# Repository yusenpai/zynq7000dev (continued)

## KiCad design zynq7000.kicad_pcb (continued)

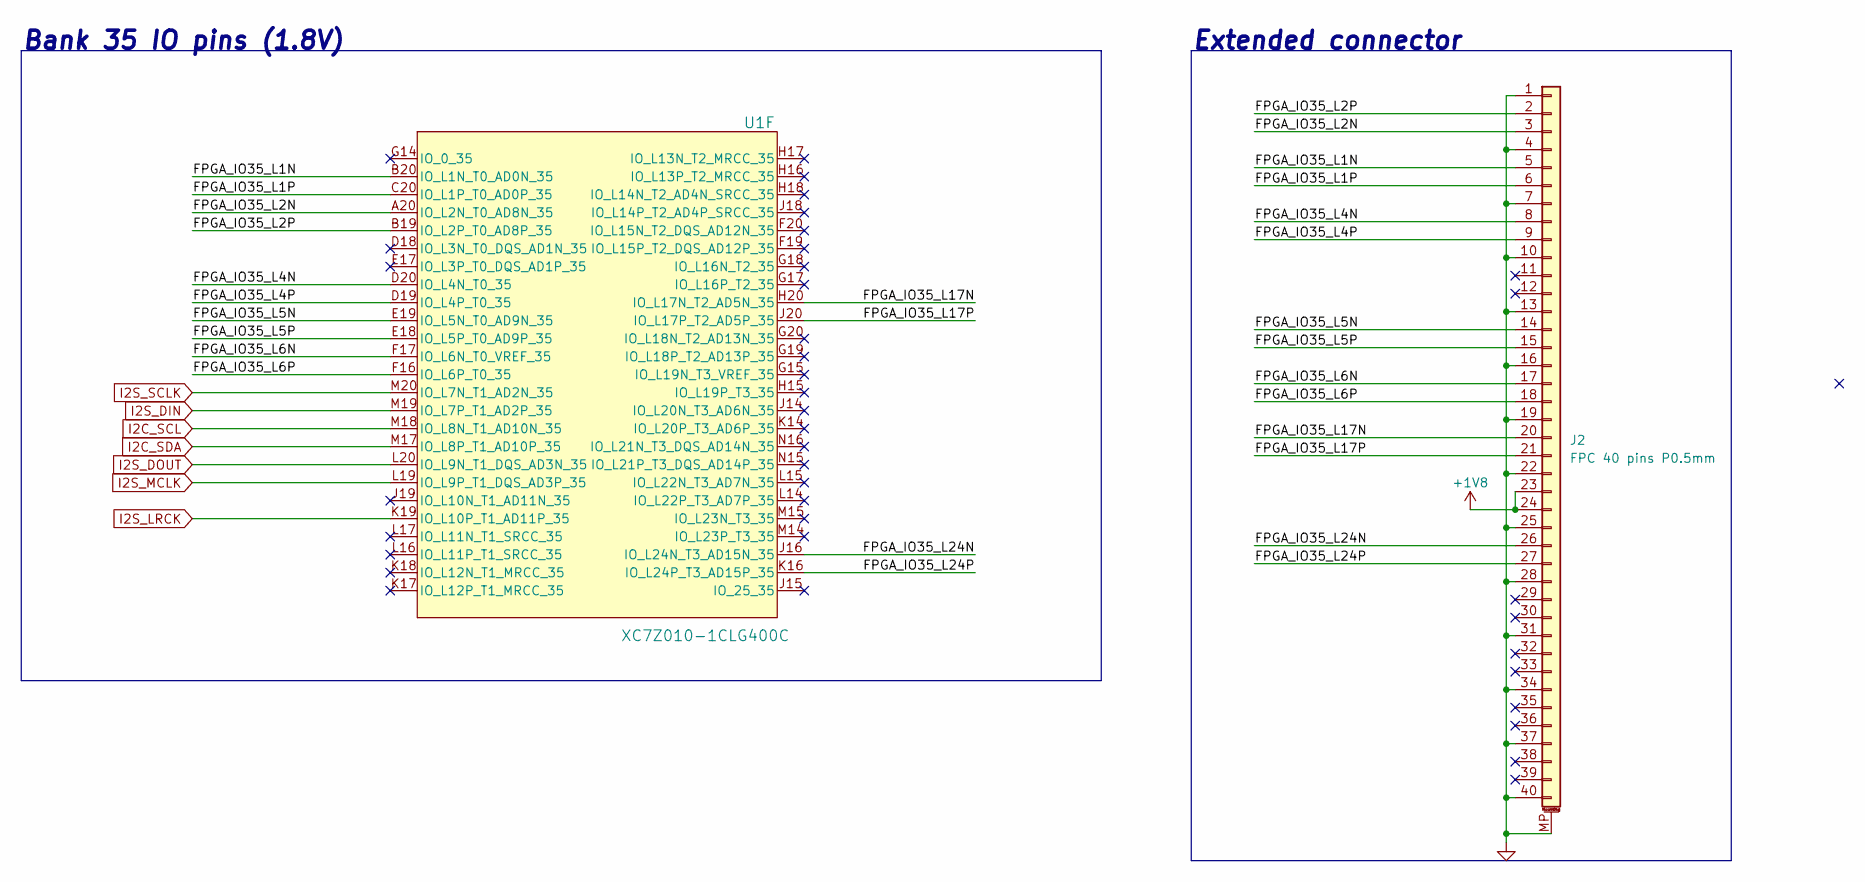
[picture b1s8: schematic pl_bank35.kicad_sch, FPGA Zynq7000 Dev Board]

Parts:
J2: FPC 40 pins P0.5mm; Amphenol_F32Q-1A7x1-11040_1x40-1MP_P0.5mm_Horizontal
U1: XC7Z010-1CLG400C; CLG400_XIL-L

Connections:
+1V8: J2.23, J2.24; also elsewhere on the board
/Bank 35 (1.8V)/FPGA_IO35_L1N: J2.5, U1.B20 (IO_L1N_T0_AD0N_35)
/Bank 35 (1.8V)/FPGA_IO35_L1P: J2.6, U1.C20 (IO_L1P_T0_AD0P_35)
/Bank 35 (1.8V)/FPGA_IO35_L2N: J2.3, U1.A20 (IO_L2N_T0_AD8N_35)
/Bank 35 (1.8V)/FPGA_IO35_L2P: J2.2, U1.B19 (IO_L2P_T0_AD8P_35)
/Bank 35 (1.8V)/FPGA_IO35_L4N: J2.8, U1.D20 (IO_L4N_T0_35)
/Bank 35 (1.8V)/FPGA_IO35_L4P: J2.9, U1.D19 (IO_L4P_T0_35)
/Bank 35 (1.8V)/FPGA_IO35_L5N: J2.14, U1.E19 (IO_L5N_T0_AD9N_35)
/Bank 35 (1.8V)/FPGA_IO35_L5P: J2.15, U1.E18 (IO_L5P_T0_AD9P_35)
/Bank 35 (1.8V)/FPGA_IO35_L6N: J2.17, U1.F17 (IO_L6N_T0_VREF_35)
/Bank 35 (1.8V)/FPGA_IO35_L6P: J2.18, U1.F16 (IO_L6P_T0_35)
/Bank 35 (1.8V)/FPGA_IO35_L17N: J2.20, U1.H20 (IO_L17N_T2_AD5N_35)
/Bank 35 (1.8V)/FPGA_IO35_L17P: J2.21, U1.J20 (IO_L17P_T2_AD5P_35)
/Bank 35 (1.8V)/FPGA_IO35_L24N: J2.26, U1.J16 (IO_L24N_T3_AD15N_35)
/Bank 35 (1.8V)/FPGA_IO35_L24P: J2.27, U1.K16 (IO_L24P_T3_AD15P_35)
GND: J2.1, J2.4, J2.7, J2.10, J2.13, J2.16, J2.19, J2.22, J2.25, J2.28, J2.31, J2.34, J2.37, J2.40, J2.MP (MountPin); also elsewhere on the board
I2C_SCL: U1.M18 (IO_L8N_T1_AD10N_35); also elsewhere on the board
I2C_SDA: U1.M17 (IO_L8P_T1_AD10P_35); also elsewhere on the board
I2S_DIN: U1.M19 (IO_L7P_T1_AD2P_35); also elsewhere on the board
I2S_DOUT: U1.L20 (IO_L9N_T1_DQS_AD3N_35); also elsewhere on the board
I2S_LRCK: U1.K19 (IO_L10P_T1_AD11P_35); also elsewhere on the board
I2S_MCLK: U1.L19 (IO_L9P_T1_DQS_AD3P_35); also elsewhere on the board
I2S_SCLK: U1.M20 (IO_L7N_T1_AD2N_35); also elsewhere on the board

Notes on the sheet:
Extended connector
Bank 35 IO pins (1.8V)

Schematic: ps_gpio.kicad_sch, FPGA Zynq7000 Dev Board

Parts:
C47: 100n; C_0402_1005Metric
D4: RED; LED_0603_1608Metric
R44, R45, R46, R47, R48, R49: 22R; R_0402_1005Metric
R50, R51: 4k7; R_0402_1005Metric
R52: 1k; R_0402_1005Metric
U1: XC7Z010-1CLG400C; CLG400_XIL-L

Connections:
+1V8: R50.1; also elsewhere on the board
/PS IO pins/ETH_TXCTL_R: R49.1, U1.F14 (PS_MIO21_501)
/PS IO pins/ETH_TXC_R: R44.1, U1.A19 (PS_MIO16_501)
/PS IO pins/ETH_TXD0_R: R45.1, U1.E14 (PS_MIO17_501)
/PS IO pins/ETH_TXD1_R: R46.1, U1.B18 (PS_MIO18_501)
/PS IO pins/ETH_TXD2_R: R47.1, U1.D10 (PS_MIO19_501)
/PS IO pins/ETH_TXD3_R: R48.1, U1.A17 (PS_MIO20_501)
ETH_MDCK: U1.C10 (PS_MIO52_501); also elsewhere on the board
ETH_MDIO: U1.C11 (PS_MIO53_501); also elsewhere on the board
ETH_RXCK: U1.B17 (PS_MIO22_501); also elsewhere on the board
ETH_RXCT: U1.D13 (PS_MIO27_501); also elsewhere on the board
ETH_RXD0: U1.D11 (PS_MIO23_501); also elsewhere on the board
ETH_RXD1: U1.A16 (PS_MIO24_501); also elsewhere on the board
ETH_RXD2: U1.F15 (PS_MIO25_501); also elsewhere on the board
ETH_RXD3: U1.A15 (PS_MIO26_501); also elsewhere on the board
ETH_TXCK: R44.2; also elsewhere on the board
ETH_TXCT: R49.2; also elsewhere on the board
ETH_TXD0: R45.2; also elsewhere on the board
ETH_TXD1: R46.2; also elsewhere on the board
ETH_TXD2: R47.2; also elsewhere on the board
ETH_TXD3: R48.2; also elsewhere on the board
FPGA_PS_VMODE1: U1.D5 (PS_MIO8_500); also elsewhere on the board
GND: C47.2, D4.1 (K), R51.2; also elsewhere on the board
unnamed: D4.2 (A), R52.2
unnamed: C47.1, R50.2, R51.1, U1.E11 (PS_MIO_VREF_501)
PS_LED: R52.1, U1.D8 (PS_MIO7_500); also elsewhere on the board
QSPI0_CK: U1.A5 (PS_MIO6_500); also elsewhere on the board
QSPI0_CSN: U1.A7 (PS_MIO1_500); also elsewhere on the board
QSPI0_D0: U1.B8 (PS_MIO2_500); also elsewhere on the board
QSPI0_D1: U1.D6 (PS_MIO3_500); also elsewhere on the board
QSPI0_D2: U1.B7 (PS_MIO4_500); also elsewhere on the board
QSPI0_D3: U1.A6 (PS_MIO5_500); also elsewhere on the board
SDIO1_CD: U1.E6 (PS_MIO0_500); also elsewhere on the board
SDIO1_CLK: U1.D9 (PS_MIO12_500); also elsewhere on the board
SDIO1_CMD: U1.C6 (PS_MIO11_500); also elsewhere on the board
SDIO1_D0: U1.E9 (PS_MIO10_500); also elsewhere on the board
SDIO1_D1: U1.E8 (PS_MIO13_500); also elsewhere on the board
SDIO1_D2: U1.C5 (PS_MIO14_500); also elsewhere on the board
SDIO1_D3: U1.C8 (PS_MIO15_500); also elsewhere on the board
ULPI_CLK: U1.B12 (PS_MIO48_501); also elsewhere on the board
ULPI_D0: U1.F13 (PS_MIO44_501); also elsewhere on the board
ULPI_D1: U1.B15 (PS_MIO45_501); also elsewhere on the board
ULPI_D2: U1.D16 (PS_MIO46_501); also elsewhere on the board
ULPI_D3: U1.B14 (PS_MIO47_501); also elsewhere on the board
ULPI_D4: U1.D14 (PS_MIO40_501); also elsewhere on the board
ULPI_D5: U1.C12 (PS_MIO49_501); also elsewhere on the board
ULPI_D6: U1.B13 (PS_MIO50_501); also elsewhere on the board
ULPI_D7: U1.B9 (PS_MIO51_501); also elsewhere on the board
ULPI_DIR: U1.C17 (PS_MIO41_501); also elsewhere on the board
ULPI_NXT: U1.A9 (PS_MIO43_501); also elsewhere on the board
ULPI_STP: U1.E12 (PS_MIO42_501); also elsewhere on the board

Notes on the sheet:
PS IO pins

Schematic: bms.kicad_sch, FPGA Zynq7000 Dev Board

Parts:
C85, C88, C90, C91: 4u7; C_0402_1005Metric
C86: 47n; C_0402_1005Metric
C87: 10u; C_0603_1608Metric
C89: 10u; C_0402_1005Metric
D5: BLUE; LED_0603_1608Metric
D6: GREEN; LED_0603_1608Metric
J6: USB_C_Receptacle_USB2.0_16P; USB_C_Receptacle_GCT_USB4105-xx-A_16P_TopMnt_Horizontal
J7: MX_1.25mm; Molex_PicoBlade_53398-0671_1x06-1MP_P1.25mm_Vertical
L6: 1u; L_Chilisin_BMRA00040420
R61, R62, R66: 5k1; R_0402_1005Metric
R63: 0R; R_0402_1005Metric; not fitted
R64, R65: 2k2; R_0402_1005Metric
R67: 30k; R_0402_1005Metric
U5: BQ25601; WQFN-24-1EP_4x4mm_P0.5mm_BQ25601

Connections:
+BATT: C89.1, J7.1, J7.2, U5.13 (BAT), U5.14 (BAT)
/BMS/BATT_THER: J7.5, R66.2, R67.1, U5.11 (TS)
GND: C85.2, C87.2, C88.2, C89.2, C90.2, C91.2, J6.A1 (GND), J6.A12 (GND), J6.B1 (GND), J6.B12 (GND), J6.S1 (SHIELD), J7.3, J7.4, R61.1, R62.1, R67.2, U5.2 (PSEL), U5.9 (~CE), U5.17 (GND), U5.18 (GND), U5.25 (GND); also elsewhere on the board
unnamed: C86.1, L6.1, U5.19 (SW), U5.20 (SW)
unnamed: D5.1 (K), R64.2
unnamed: D6.1 (K), R65.1
unnamed: J6.A5 (CC1), R61.2
unnamed: J6.B5 (CC2), R62.2
unnamed: J6.A6 (D+), J6.B6 (D+), R63.2
unnamed: J6.A7 (D-), J6.B7 (D-), R63.1
unnamed: C86.2, U5.21 (BTST)
unnamed: C90.1, C91.1, U5.23 (PMID)
unnamed: C88.1, R66.1, U5.22 (REGN)
unnamed: R64.1, U5.4 (STAT)
unnamed: R65.2, U5.3 (~PG)
PMIC_I2C_SCL: U5.5 (SCL); also elsewhere on the board
PMIC_I2C_SDA: U5.6 (SDA); also elsewhere on the board
PMIC_PWRON: U5.12 (~QON); also elsewhere on the board
VBUS: C85.1, J6.A4 (VBUS), J6.A9 (VBUS), J6.B4 (VBUS), J6.B9 (VBUS), U5.1 (VAC), U5.24 (VBUS)
VSYS: C87.1, D5.2 (A), D6.2 (A), L6.2, U5.15 (SYS), U5.16 (SYS); also elsewhere on the board

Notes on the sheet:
PSEL = 0 : ILIM = 2.4A CE = 0 : charge enable PMIC_PWRON = 0 for 1s: BATFET turn on. PMIC turn on. PMIC_PWRON = 0 for 4s: PMIC turn off. PMIC_PWRON = 0 for 8s: system reset.
BMS

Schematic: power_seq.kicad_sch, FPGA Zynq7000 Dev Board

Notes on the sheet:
+1.0V
From PMIC
BUCK
+3.3V
1.4A
LDO
PS: AUX, PLL, Bank 501 PL: AUX, Bank 35 USB PHY, ETH PHY, Audio CODEC
6A discharge 2A charge
4.5A
PS: Bank 502 2xDDR3 DRAM
0.5A
0.8A
+1.35V
+0.675V
DDR3L VTT rail
From BMS
Power Sequence
Power up: 1 -> 2 -> 3 -> 4 Power down: 4 -> 3 -> 2 -> 1
USB-C Connector
+5V
+1.8V
1.25A
0.2A
Power Tree
PS: Bank 500 PL: Bank 34 QSPI Flash, SD Card
DDR3L reference
1.1A
Ramp-up time must be smaller than 50ms
BMS
Battery
+3.5V -> +4.2V
0.6A
+3.5V
PS: Internal PL: Internal, BRAM
3.5V
3.8A
Audio CODEC

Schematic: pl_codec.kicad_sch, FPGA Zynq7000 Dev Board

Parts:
C48, C49, C50, C51, C54: 100n; C_0402_1005Metric
C52, C53, C55: 1u; C_0402_1005Metric
C56, C57: 22u; C_0603_1608Metric
J4: PJ320D; Jack_3.5mm_PJ320D_Horizontal
R53: 2k2; R_0402_1005Metric
R54, R55: 4k7; R_0402_1005Metric
U4: SGTL5000XNLA3; QFN-20-1EP_3x3mm_P0.4mm_EP1.65x1.65mm

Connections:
+1V8: C48.1, C49.1, R54.1, R55.1, U4.12 (VDDIO), U4.20 (VDDD); also elsewhere on the board
+1V8A: C50.1, U4.3 (VDDA); also elsewhere on the board
/Audio CODEC/LINEIN_L: C53.1, C57.2, J4.T
/Audio CODEC/LINEIN_R: C52.1, C56.2, J4.R1
/Audio CODEC/MIC_IN: C54.1, J4.S, R53.1
GND: C48.2, C49.2, C50.2, C51.1, C55.2, U4.21 (GND); also elsewhere on the board
I2C_SCL: R55.2, U4.19 (CTRL_CLK); also elsewhere on the board
I2C_SDA: R54.2, U4.18 (CTRL_DATA); also elsewhere on the board
I2S_DIN: U4.17 (I2S_DIN); also elsewhere on the board
I2S_DOUT: U4.16 (I2S_DOUT); also elsewhere on the board
I2S_LRCK: U4.14 (I2S_LRCLK); also elsewhere on the board
I2S_MCLK: U4.13 (SYS_MCLK); also elsewhere on the board
I2S_SCLK: U4.15 (I2S_SCLK); also elsewhere on the board
unnamed: C57.1, U4.4 (HP_L)
unnamed: C56.1, U4.1 (HP_R)
unnamed: J4.R2, U4.2 (HP_VGND)
unnamed: C53.2, U4.9 (LINEIN_L)
unnamed: C52.2, U4.8 (LINEIN_R)
unnamed: C54.2, U4.10 (MIC)
unnamed: C55.1, R53.2, U4.11 (MIC_BIAS)
unnamed: C51.2, U4.5 (VAG)

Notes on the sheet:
Audio CODEC

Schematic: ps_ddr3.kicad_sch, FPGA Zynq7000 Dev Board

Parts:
C1, C2, C3, C4, C5, C6, C7, C8, C10, C11, C12, C13, C14, C15, C16, C17, C18, C19, C20, C21, C22, C23, C24, C25, C26: 1u; C_0402_1005Metric
C9: 470n; C_0402_1005Metric; not fitted
C29, C30: 10u; C_0402_1005Metric
C31, C32: 4u7; C_0402_1005Metric
C33, C34, C35, C36, C37, C38, C39, C40, C41, C42, C43, C44: 100n; C_0402_1005Metric
R3, R4: 240R; R_0402_1005Metric
R6, R7, R8: 4k7; R_0402_1005Metric
R9, R10, R11, R12, R13, R14, R15, R16, R17, R18, R20, R21, R22, R23, R24, R25, R26, R27, R28, R29, R30, R31, R32, R33: 60R4; R_0402_1005Metric
R19: 120R; R_0402_1005Metric
U2, U3: H5TC2G83EFR-xxA; FBGA-78_7.5x11mm_Layout2x3x13_P0.8mm

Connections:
+0V675: C29.1, C30.1, C31.1, C32.1, C33.1, C34.1, C35.1, C36.1, C37.1, C38.1, C39.1, C40.1, C41.1, C42.1, C43.1, C44.1, R9.1, R10.1, R11.1, R12.1, R13.1, R14.1, R15.1, R16.1, R17.1, R18.1, R20.1, R21.1, R22.1, R23.1, R24.1, R25.1, R26.1, R27.1, R28.1, R29.1, R30.1, R31.1, R32.1, R33.1; also elsewhere on the board
+1V35: C1.1, C2.1, C3.1, C4.1, C5.1, C6.1, C7.1, C8.1, C9.1, C10.1, C11.1, C12.1, C13.1, C14.1, C15.1, C16.1, C17.1, C18.1, C19.1, C20.1, C21.1, C22.1, C23.1, C24.1, U2.A2 (VDD), U2.A9 (VDD), U2.B9 (VDDQ), U2.C1 (VDDQ), U2.D7 (VDD), U2.E2 (VDDQ), U2.E9 (VDDQ), U2.G2 (VDD), U2.G8 (VDD), U2.K1 (VDD), U2.K9 (VDD), U2.M1 (VDD), U2.M9 (VDD), U3.A2 (VDD), U3.A9 (VDD), U3.B9 (VDDQ), U3.C1 (VDDQ), U3.D7 (VDD), U3.E2 (VDDQ), U3.E9 (VDDQ), U3.G2 (VDD), U3.G8 (VDD), U3.K1 (VDD), U3.K9 (VDD), U3.M1 (VDD), U3.M9 (VDD); also elsewhere on the board
DRAM_A0: R16.2, U2.K3 (A0), U3.K3 (A0); also elsewhere on the board
DRAM_A1: R18.2, U2.L7 (A1), U3.L7 (A1); also elsewhere on the board
DRAM_A2: R21.2, U2.L3 (A2), U3.L3 (A2); also elsewhere on the board
DRAM_A3: R23.2, U2.K2 (A3), U3.K2 (A3); also elsewhere on the board
DRAM_A4: R25.2, U2.L8 (A4), U3.L8 (A4); also elsewhere on the board
DRAM_A5: R27.2, U2.L2 (A5), U3.L2 (A5); also elsewhere on the board
DRAM_A6: R29.2, U2.M8 (A6), U3.M8 (A6); also elsewhere on the board
DRAM_A7: R31.2, U2.M2 (A7), U3.M2 (A7); also elsewhere on the board
DRAM_A8: R33.2, U2.N8 (A8), U3.N8 (A8); also elsewhere on the board
DRAM_A9: R9.2, U2.M3 (A9), U3.M3 (A9); also elsewhere on the board
DRAM_A10: R11.2, U2.H7 (A10/AP), U3.H7 (A10/AP); also elsewhere on the board
DRAM_A11: R13.2, U2.M7 (A11), U3.M7 (A11); also elsewhere on the board
DRAM_A12: R15.2, U2.K7 (A12/BC#), U3.K7 (A12/BC#); also elsewhere on the board
DRAM_A13: R17.2, U2.N3 (A13), U3.N3 (A13); also elsewhere on the board
DRAM_A14: R20.2, U2.N7 (A14), U3.N7 (A14); also elsewhere on the board
DRAM_BA0: R10.2, U2.J2 (BA0), U3.J2 (BA0); also elsewhere on the board
DRAM_BA1: R12.2, U2.K8 (BA1), U3.K8 (BA1); also elsewhere on the board
DRAM_BA2: R14.2, U2.J3 (BA2), U3.J3 (BA2); also elsewhere on the board
DRAM_CASN: R28.2, U2.G3 (CAS#), U3.G3 (CAS#); also elsewhere on the board
DRAM_CKE: R6.1, R22.2, U2.G9 (CKE), U3.G9 (CKE); also elsewhere on the board
DRAM_CLK_N: R19.2, U2.G7 (CK#), U3.G7 (CK#); also elsewhere on the board
DRAM_CLK_P: R19.1, U2.F7 (CK), U3.F7 (CK); also elsewhere on the board
DRAM_CSN: R7.1, R32.2, U2.H2 (CS#), U3.H2 (CS#); also elsewhere on the board
DRAM_DM0: U2.B7 (DM/TDQS); also elsewhere on the board
DRAM_DM1: U3.B7 (DM/TDQS); also elsewhere on the board
DRAM_DQ0: U2.B3 (DQ0); also elsewhere on the board
DRAM_DQ1: U2.C7 (DQ1); also elsewhere on the board
DRAM_DQ2: U2.D2 (DQ6); also elsewhere on the board
DRAM_DQ3: U2.C8 (DQ3); also elsewhere on the board
DRAM_DQ4: U2.E3 (DQ4); also elsewhere on the board
DRAM_DQ5: U2.E8 (DQ5); also elsewhere on the board
DRAM_DQ6: U2.C2 (DQ2); also elsewhere on the board
DRAM_DQ7: U2.E7 (DQ7); also elsewhere on the board
DRAM_DQ8: U3.B3 (DQ0); also elsewhere on the board
DRAM_DQ9: U3.C7 (DQ1); also elsewhere on the board
DRAM_DQ10: U3.C2 (DQ2); also elsewhere on the board
DRAM_DQ11: U3.C8 (DQ3); also elsewhere on the board
DRAM_DQ12: U3.E3 (DQ4); also elsewhere on the board
DRAM_DQ13: U3.E8 (DQ5); also elsewhere on the board
DRAM_DQ14: U3.D2 (DQ6); also elsewhere on the board
DRAM_DQ15: U3.E7 (DQ7); also elsewhere on the board
DRAM_DQS0_N: U2.D3 (DQS#); also elsewhere on the board
DRAM_DQS0_P: U2.C3 (DQS); also elsewhere on the board
DRAM_DQS1_N: U3.D3 (DQS#); also elsewhere on the board
DRAM_DQS1_P: U3.C3 (DQS); also elsewhere on the board
DRAM_ODT: R30.2, U2.G1 (ODT), U3.G1 (ODT); also elsewhere on the board
DRAM_RASN: R26.2, U2.F3 (RAS#), U3.F3 (RAS#); also elsewhere on the board
DRAM_RSTN: R8.1, U2.N2 (RESET#), U3.N2 (RESET#); also elsewhere on the board
DRAM_WEN: R24.2, U2.H3 (WE#), U3.H3 (WE#); also elsewhere on the board
GND: C1.2, C2.2, C3.2, C4.2, C5.2, C6.2, C7.2, C8.2, C9.2, C10.2, C11.2, C12.2, C13.2, C14.2, C15.2, C16.2, C17.2, C18.2, C19.2, C20.2, C21.2, C22.2, C23.2, C24.2, C25.2, C26.2, C29.2, C30.2, C31.2, C32.2, C33.2, C34.2, C35.2, C36.2, C37.2, C38.2, C39.2, C40.2, C41.2, C42.2, C43.2, C44.2, R3.2, R4.2, R6.2, R7.2, R8.2, U2.A1 (VSS), U2.A8 (VSS), U2.B1 (VSS), U2.B2 (VSSQ), U2.B8 (VSSQ), U2.C9 (VSSQ), U2.D1 (VSSQ), U2.D8 (VSS), U2.D9 (VSSQ), U2.F2 (VSS), U2.F8 (VSS), U2.J1 (VSS), U2.J9 (VSS), U2.L1 (VSS), U2.L9 (VSS), U2.N1 (VSS), U2.N9 (VSS), U3.A1 (VSS), U3.A8 (VSS), U3.B1 (VSS), U3.B2 (VSSQ), U3.B8 (VSSQ), U3.C9 (VSSQ), U3.D1 (VSSQ), U3.D8 (VSS), U3.D9 (VSSQ), U3.F2 (VSS), U3.F8 (VSS), U3.J1 (VSS), U3.J9 (VSS), U3.L1 (VSS), U3.L9 (VSS), U3.N1 (VSS), U3.N9 (VSS); also elsewhere on the board
unnamed: R3.1, U2.H8 (ZQ)
unnamed: R4.1, U3.H8 (ZQ)
VREF_DDR: C25.1, C26.1, U2.E1 (VREFDQ), U2.J8 (VREFCA), U3.E1 (VREFDQ), U3.J8 (VREFCA); also elsewhere on the board

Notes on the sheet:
need termination for data mask ?
DDR3L-2
DDR3L-1
VTT bypass cap. and termination

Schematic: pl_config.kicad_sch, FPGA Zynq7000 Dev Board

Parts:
C45, C46: 100n; C_0402_1005Metric
D1: RED; LED_0603_1608Metric
D2: GREEN; LED_0603_1608Metric
D3: BLUE; LED_0603_1608Metric
J3: Header 2.54mm; PinHeader_1x06_P2.54mm_Vertical
R34, R36, R37: 10k; R_0402_1005Metric
R35, R38, R40, R43: 4k7; R_0402_1005Metric
R39, R41: 1k; R_0402_1005Metric
R42: 330R; R_0402_1005Metric
SW1, SW2: SW_Push; SW_Push_1P1T_NO_Vertical_Wuerth_434133025816
U1: XC7Z010-1CLG400C; CLG400_XIL-L

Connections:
+3V3: R34.1, R35.1, R36.1, R37.1, R38.1, R39.1, R40.2, R42.1, U1.M6 (CFGBVS_0); also elsewhere on the board
/PL Configuration/FPGA_PL_DONE: D3.2 (A), R42.2, U1.R11 (DONE_0)
/PL Configuration/FPGA_PL_INIT_B: D1.1 (K), D2.2 (A), R39.2, U1.R10 (INIT_B_0)
/PL Configuration/FPGA_PL_PROGRAM_B: C45.2, R38.2, SW1.2, U1.L6 (PROGRAM_B_0)
FPGA_PS_CLK_40MHz: U1.E7 (PS_CLK_500); also elsewhere on the board
FPGA_PS_SRST_B: C46.2, J3.1, R35.2, SW2.2, U1.B10 (PS_SRST_B_501); also elsewhere on the board
FPGA_TCK: J3.2, R36.2, U1.F9 (TCK_0); also elsewhere on the board
FPGA_TDI: J3.4, U1.G6 (TDI_0); also elsewhere on the board
FPGA_TDO: J3.3, U1.F6 (TDO_0); also elsewhere on the board
FPGA_TMS: J3.5, R37.2, U1.J6 (TMS_0); also elsewhere on the board
GND: C45.1, C46.1, J3.6, R41.2, R43.2, SW1.1, SW2.1; also elsewhere on the board
unnamed: D1.2 (A), R40.1
unnamed: D2.1 (K), R41.1
unnamed: D3.1 (K), R43.1
PMIC_MCU_NRST: R34.2, U1.C7 (PS_POR_B_500); also elsewhere on the board

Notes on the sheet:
PL Configuration
Configuration Block and JTAG conn.
OK PS_POR_B input is required to be asserted to GND during the power-on sequence OK The PS system reset (PS_SRST_B) is an active-Low signal that is mostly used for debugging proposes. OK PS_SRST_B must be High to begin the boot process OK 30MHz < PS_CLK < 60MHz OK TMS and TCK have 10k pull up OK PR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
DONE = 1: Done configuration INIT_B = 0: Open-drain, initialization of configuration memory PROGRAM_B = 0: Asynchronous reset of configuration logic CFGBVS = VCCO_0: MUST DO. Select the voltage level of 3.3V for configuration bank

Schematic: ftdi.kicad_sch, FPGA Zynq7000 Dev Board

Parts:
C157, C168: 4u7; C_0402_1005Metric
C158, C159, C160, C161, C162, C163, C164, C165, C166, C167, C169: 100n; C_0402_1005Metric
C170, C171: 10p; C_0402_1005Metric
FB1: 600R; L_0603_1608Metric
J11: USB_C_Receptacle_USB2.0_16P; USB_C_Receptacle_GCT_USB4105-xx-A_16P_TopMnt_Horizontal
R87, R88: 5k1; R_0402_1005Metric
R89, R95: 2k; R_0402_1005Metric
R90, R92, R93, R94: 10k; R_0402_1005Metric
R91: 1k; R_0402_1005Metric
U9: FT4232H; LQFP-64_10x10mm_P0.5mm
U10: AT93C46-10SU-2.7-T; SOIC8_4P9X3P9MC_MCH
Y2: 12MHz; Crystal_SMD_3225-4Pin_3.2x2.5mm

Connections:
+1V8_FTDI: C165.1, C166.1, C167.1, C168.1, U9.12 (VCORE), U9.37 (VCORE), U9.49 (VREGOUT), U9.64 (VCORE)
+3V3: C160.1, C161.1, C162.1, C163.1, C164.1, C169.1, FB1.1, R91.1, R92.1, R93.1, R94.1, U9.20 (VCCIO), U9.21 (ADBUS4), U9.31 (VCCIO), U9.42 (VCCIO), U9.50 (VREGIN), U9.56 (VCCIO), U10.2 (VCC), U10.8 (ORG); also elsewhere on the board
+3V3_PLL: C157.1, C158.1, C159.1, FB1.2, U9.4 (VPHY), U9.9 (VPLL)
/FTDI/FTDI_EEPROM_CS: R92.2, U9.63 (EECS), U10.3 (CS)
/FTDI/FTDI_EEPROM_DATA: R95.2, U9.61 (EEDATA), U10.5 (DI)
/FTDI/FTDI_EEPROM_SCK: R93.2, U9.62 (EECLK), U10.4 (SK)
/FTDI/USB_JTAG_D+: J11.A6 (D+), J11.B6 (D+), U9.8 (DP)
/FTDI/USB_JTAG_D-: J11.A7 (D-), J11.B7 (D-), U9.7 (DM)
FPGA_PS_SRST_B: U9.23 (ADBUS6); also elsewhere on the board
FPGA_TCK: U9.16 (ADBUS0); also elsewhere on the board
FPGA_TDI: U9.17 (ADBUS1); also elsewhere on the board
FPGA_TDO: U9.18 (ADBUS2); also elsewhere on the board
FPGA_TMS: U9.19 (ADBUS3); also elsewhere on the board
GND: C157.2, C158.2, C159.2, C160.2, C161.2, C162.2, C163.2, C164.2, C165.2, C166.2, C167.2, C168.2, C169.2, C170.2, C171.2, J11.A1 (GND), J11.A12 (GND), J11.B1 (GND), J11.B12 (GND), R87.2, R88.2, R89.2, U9.1 (GND), U9.5 (GND), U9.10 (AGND), U9.11 (GND), U9.13 (TEST), U9.15 (GND), U9.25 (GND), U9.35 (GND), U9.47 (GND), U9.51 (GND), U10.7 (GND), Y2.2, Y2.4; also elsewhere on the board
unnamed: J11.A5 (CC1), R87.1
unnamed: J11.B5 (CC2), R88.1
unnamed: R89.1, R90.2
unnamed: C170.1, U9.2 (OSCI), Y2.3
unnamed: C171.1, U9.3 (OSCO), Y2.1
unnamed: R90.1, U9.6 (REF)
unnamed: R91.2, U9.14 (~RESET)
unnamed: R94.2, R95.1, U10.6 (DO)
UART1_RX: U9.26 (BDBUS0); also elsewhere on the board
UART1_TX: U9.27 (BDBUS1); also elsewhere on the board
UART2_RX: U9.38 (CDBUS0); also elsewhere on the board
UART2_TX: U9.39 (CDBUS1); also elsewhere on the board
UART3_RX: U9.48 (DDBUS0); also elsewhere on the board
UART3_TX: U9.52 (DDBUS1); also elsewhere on the board

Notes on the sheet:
FTDI USB-JTAG

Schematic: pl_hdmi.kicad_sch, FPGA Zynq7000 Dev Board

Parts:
J12: HDMI_A_1.4; HDMI_A_Molex_208658-1001_Horizontal
Q1, Q2, Q3: 2N7002; SOT-23
R96, R97, R98, R99, R100: 4k7; R_0402_1005Metric

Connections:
+3V3: Q1.1 (G), Q2.1 (G), R96.1, R97.1, R100.1; also elsewhere on the board
/HDMI/HDMI_HPD: J12.19 (HPD/HEAC-), Q3.1 (G)
/HDMI/HDMI_I2C_SCL_50: J12.15 (SCL), Q1.3 (D), R99.2
/HDMI/HDMI_I2C_SDA_50: J12.16 (SDA), Q2.3 (D), R98.2
GND: J12.2 (D2S), J12.5 (D1S), J12.8 (D0S), J12.11 (CKS), J12.17 (GND), J12.SH, Q3.2 (S); also elsewhere on the board
HDMI_CEC: J12.13 (CEC); also elsewhere on the board
HDMI_CLK_N: J12.12 (CK-); also elsewhere on the board
HDMI_CLK_P: J12.10 (CK+); also elsewhere on the board
HDMI_DAT0_N: J12.9 (D0-); also elsewhere on the board
HDMI_DAT0_P: J12.7 (D0+); also elsewhere on the board
HDMI_DAT1_N: J12.6 (D1-); also elsewhere on the board
HDMI_DAT1_P: J12.4 (D1+); also elsewhere on the board
HDMI_DAT2_N: J12.3 (D2-); also elsewhere on the board
HDMI_DAT2_P: J12.1 (D2+); also elsewhere on the board
HDMI_HP_DET: Q3.3 (D), R100.2; also elsewhere on the board
HDMI_I2C_SCL: Q1.2 (S), R96.2; also elsewhere on the board
HDMI_I2C_SDA: Q2.2 (S), R97.2; also elsewhere on the board
VBUS1: J12.18 (+5V), R98.1, R99.1; also elsewhere on the board

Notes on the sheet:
HDMI

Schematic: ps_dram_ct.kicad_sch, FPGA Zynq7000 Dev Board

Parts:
C27, C28: 100n; C_0402_1005Metric
R2, R5: 120R; R_0402_1005Metric
U1: XC7Z010-1CLG400C; CLG400_XIL-L

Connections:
+1V35: R2.1; also elsewhere on the board
DRAM_A0: U1.N2 (PS_DDR_A0_502); also elsewhere on the board
DRAM_A1: U1.K2 (PS_DDR_A1_502); also elsewhere on the board
DRAM_A2: U1.M3 (PS_DDR_A2_502); also elsewhere on the board
DRAM_A3: U1.K3 (PS_DDR_A3_502); also elsewhere on the board
DRAM_A4: U1.M4 (PS_DDR_A4_502); also elsewhere on the board
DRAM_A5: U1.L1 (PS_DDR_A5_502); also elsewhere on the board
DRAM_A6: U1.L4 (PS_DDR_A6_502); also elsewhere on the board
DRAM_A7: U1.K4 (PS_DDR_A7_502); also elsewhere on the board
DRAM_A8: U1.K1 (PS_DDR_A8_502); also elsewhere on the board
DRAM_A9: U1.J4 (PS_DDR_A9_502); also elsewhere on the board
DRAM_A10: U1.F5 (PS_DDR_A10_502); also elsewhere on the board
DRAM_A11: U1.G4 (PS_DDR_A11_502); also elsewhere on the board
DRAM_A12: U1.E4 (PS_DDR_A12_502); also elsewhere on the board
DRAM_A13: U1.D4 (PS_DDR_A13_502); also elsewhere on the board
DRAM_A14: U1.F4 (PS_DDR_A14_502); also elsewhere on the board
DRAM_BA0: U1.L5 (PS_DDR_BA0_502); also elsewhere on the board
DRAM_BA1: U1.R4 (PS_DDR_BA1_502); also elsewhere on the board
DRAM_BA2: U1.J5 (PS_DDR_BA2_502); also elsewhere on the board
DRAM_CASN: U1.P5 (PS_DDR_CAS_B_502); also elsewhere on the board
DRAM_CKE: U1.N3 (PS_DDR_CKE_502); also elsewhere on the board
DRAM_CLK_N: U1.M2 (PS_DDR_CKN_502); also elsewhere on the board
DRAM_CLK_P: U1.L2 (PS_DDR_CKP_502); also elsewhere on the board
DRAM_CSN: U1.N1 (PS_DDR_CS_B_502); also elsewhere on the board
DRAM_DM0: U1.A1 (PS_DDR_DM0_502); also elsewhere on the board
DRAM_DM1: U1.F1 (PS_DDR_DM1_502); also elsewhere on the board
DRAM_DQ0: U1.B3 (PS_DDR_DQ1_502); also elsewhere on the board
DRAM_DQ1: U1.D1 (PS_DDR_DQ5_502); also elsewhere on the board
DRAM_DQ2: U1.A4 (PS_DDR_DQ3_502); also elsewhere on the board
DRAM_DQ3: U1.D3 (PS_DDR_DQ4_502); also elsewhere on the board
DRAM_DQ4: U1.A2 (PS_DDR_DQ2_502); also elsewhere on the board
DRAM_DQ5: U1.E1 (PS_DDR_DQ7_502); also elsewhere on the board
DRAM_DQ6: U1.C3 (PS_DDR_DQ0_502); also elsewhere on the board
DRAM_DQ7: U1.C1 (PS_DDR_DQ6_502); also elsewhere on the board
DRAM_DQ8: U1.E3 (PS_DDR_DQ9_502); also elsewhere on the board
DRAM_DQ9: U1.H3 (PS_DDR_DQ11_502); also elsewhere on the board
DRAM_DQ10: U1.H2 (PS_DDR_DQ13_502); also elsewhere on the board
DRAM_DQ11: U1.J3 (PS_DDR_DQ12_502); also elsewhere on the board
DRAM_DQ12: U1.E2 (PS_DDR_DQ8_502); also elsewhere on the board
DRAM_DQ13: U1.J1 (PS_DDR_DQ15_502); also elsewhere on the board
DRAM_DQ14: U1.G3 (PS_DDR_DQ10_502); also elsewhere on the board
DRAM_DQ15: U1.H1 (PS_DDR_DQ14_502); also elsewhere on the board
DRAM_DQS0_N: U1.B2 (PS_DDR_DQS_N0_502); also elsewhere on the board
DRAM_DQS0_P: U1.C2 (PS_DDR_DQS_P0_502); also elsewhere on the board
DRAM_DQS1_N: U1.F2 (PS_DDR_DQS_N1_502); also elsewhere on the board
DRAM_DQS1_P: U1.G2 (PS_DDR_DQS_P1_502); also elsewhere on the board
DRAM_ODT: U1.N5 (PS_DDR_ODT_502); also elsewhere on the board
DRAM_RASN: U1.P4 (PS_DDR_RAS_B_502); also elsewhere on the board
DRAM_RSTN: U1.B4 (PS_DDR_DRST_B_502); also elsewhere on the board
DRAM_WEN: U1.M5 (PS_DDR_WE_B_502); also elsewhere on the board
GND: C27.2, C28.2, R5.2; also elsewhere on the board
unnamed: R2.2, U1.G5 (PS_DDR_VRN_502)
unnamed: R5.1, U1.H5 (PS_DDR_VRP_502)
VREF_DDR: C27.1, C28.1, U1.H6 (PS_DDR_VREF0_502), U1.P6 (PS_DDR_VREF1_502); also elsewhere on the board

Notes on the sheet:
DRAM Controller

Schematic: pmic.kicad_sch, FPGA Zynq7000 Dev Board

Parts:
C58, C72, C75, C80: 100n; C_0402_1005Metric
C59, C60, C61, C62, C63, C64, C65: 10u; C_0402_1005Metric
C66, C67, C68, C69, C70, C71, C73, C74, C77, C78: 22u; C_0603_1608Metric
C76, C81, C82, C83, C84, C175: 1u; C_0402_1005Metric
C79, C174: 4u7; C_0402_1005Metric
IC1: MMPF0100NPAEP; QFN-56-1EP_8x8mm_P0.5mm_EP4.3x4.3mm; Manufacturer_Part_Number MMPF0100NPAEP; Mouser Part Number 841-MMPF0100NPAEP
J5: Header 2.54mm; PinHeader_1x05_P2.54mm_Vertical
L1, L2, L3, L4, L5: 1u; L_Chilisin_BMRA00040420
R56, R57: 4k7; R_0402_1005Metric
R58: 100k; R_0402_1005Metric
R59: DNP; R_0402_1005Metric
R60: DNP; R_0402_1005Metric; not fitted
SW3: SW_Push; SW_Push_1P1T_NO_Vertical_Wuerth_434133025816

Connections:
+0V675: C77.1, C78.1, IC1.19 (SW4FB), L5.2; also elsewhere on the board
+1V0: C66.1, C67.1, IC1.13 (SW1CFB), L1.2; also elsewhere on the board
+1V8: C68.1, C69.1, IC1.25 (SW2FB), L2.2; also elsewhere on the board
+1V8A: C174.1, IC1.28 (VGEN4); also elsewhere on the board
+1V35: C70.1, C71.1, C72.1, IC1.30 (VINREFDDR), IC1.38 (SW3AFB), L3.2; also elsewhere on the board
+3V3: C73.1, C74.1, C175.1, IC1.17 (VIN1), IC1.27 (VIN2), IC1.33 (SW3BFB), IC1.40 (VIN3), L4.2, R60.2; also elsewhere on the board
/PMIC/VSNVS: C81.1, IC1.43 (VSNVS), R58.1
GND: C58.1, C59.2, C60.2, C61.2, C62.2, C63.2, C64.2, C65.2, C66.2, C67.2, C68.2, C69.2, C70.2, C71.2, C73.2, C74.2, C75.2, C76.2, C77.2, C78.2, C79.2, C80.2, C81.2, C82.2, C83.2, C84.2, C174.2, C175.2, IC1.4 (STANDBY), IC1.5 (ICTEST), IC1.14 (SW1VSSSNS), IC1.15 (GNDREF), IC1.32 (SW3VSSSNS), IC1.48 (GNDREF), IC1.57 (EPAD), J5.5, R59.2, SW3.1; also elsewhere on the board
unnamed: C80.1, IC1.42 (LICELL)
unnamed: IC1.8 (SW1ALX), IC1.9 (SW1BLX), IC1.11 (SW1CLX), L1.1
unnamed: IC1.22 (SW2LX), L2.1
unnamed: IC1.36 (SW3ALX), L3.1
unnamed: IC1.35 (SW3BLX), L4.1
unnamed: IC1.21 (SW4LX), L5.1
unnamed: C84.1, IC1.49 (VCORE)
unnamed: C82.1, IC1.51 (VCOREDIG)
unnamed: C83.1, IC1.52 (VCOREREF)
unnamed: C72.2, C75.1, IC1.29 (VHALF)
PMIC_I2C_SCL: IC1.54 (SCL), J5.3, R56.2; also elsewhere on the board
PMIC_I2C_SDA: IC1.53 (SDA), J5.4, R57.2; also elsewhere on the board
PMIC_MCU_NRST: IC1.3 (RESETBMCU); also elsewhere on the board
PMIC_PWRON: C58.2, IC1.56 (PWRON), R58.2, SW3.2; also elsewhere on the board
PMIC_VDDIO: IC1.55 (VDDIO), J5.2, R56.1, R57.1, R60.1
PMIC_VDDOTP: IC1.47 (VDDOTP), J5.1, R59.1
VREF_DDR: C76.1, IC1.31 (VREFDDR); also elsewhere on the board
VSYS: C59.1, C60.1, C61.1, C62.1, C63.1, C64.1, C65.1, C79.1, IC1.7 (SW1AIN), IC1.10 (SW1BIN), IC1.12 (SW1CIN), IC1.20 (SW4IN), IC1.23 (SW2IN), IC1.24 (SW2IN), IC1.34 (SW3BIN), IC1.37 (SW3AIN), IC1.45 (SWBSTIN), IC1.50 (VIN); also elsewhere on the board

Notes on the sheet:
populate when done programing
PMIC programming header
OK INTB, SDWNB: Leave floating OK RESETBMCU. Pull up to 3.3V (< Vin) with 100k. OK STANDBY, ICTEST = GND OK SW1ABC single phase mode OK SW1FB floating OK SW1CFB real feedback OK VIN123 connected to V < 3.4V OK LICELL bypass with 0.1u OK VSNVS bypass with 0.47u OK SWBSTFB floating OK SWBSTIN to VIN 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
PMIC
SW1ABC: 1.00V, 4.50A, to Core SW2: 1.80V, 2.50A, to AUX SW3A: 1.35V, 1.25A, to DRAM SW3B: 3.30V, 1.25A, to IO SW4: .675V, 1.00A, to VTT VREFDDR: .675V, 0.01A, to DRAM reference

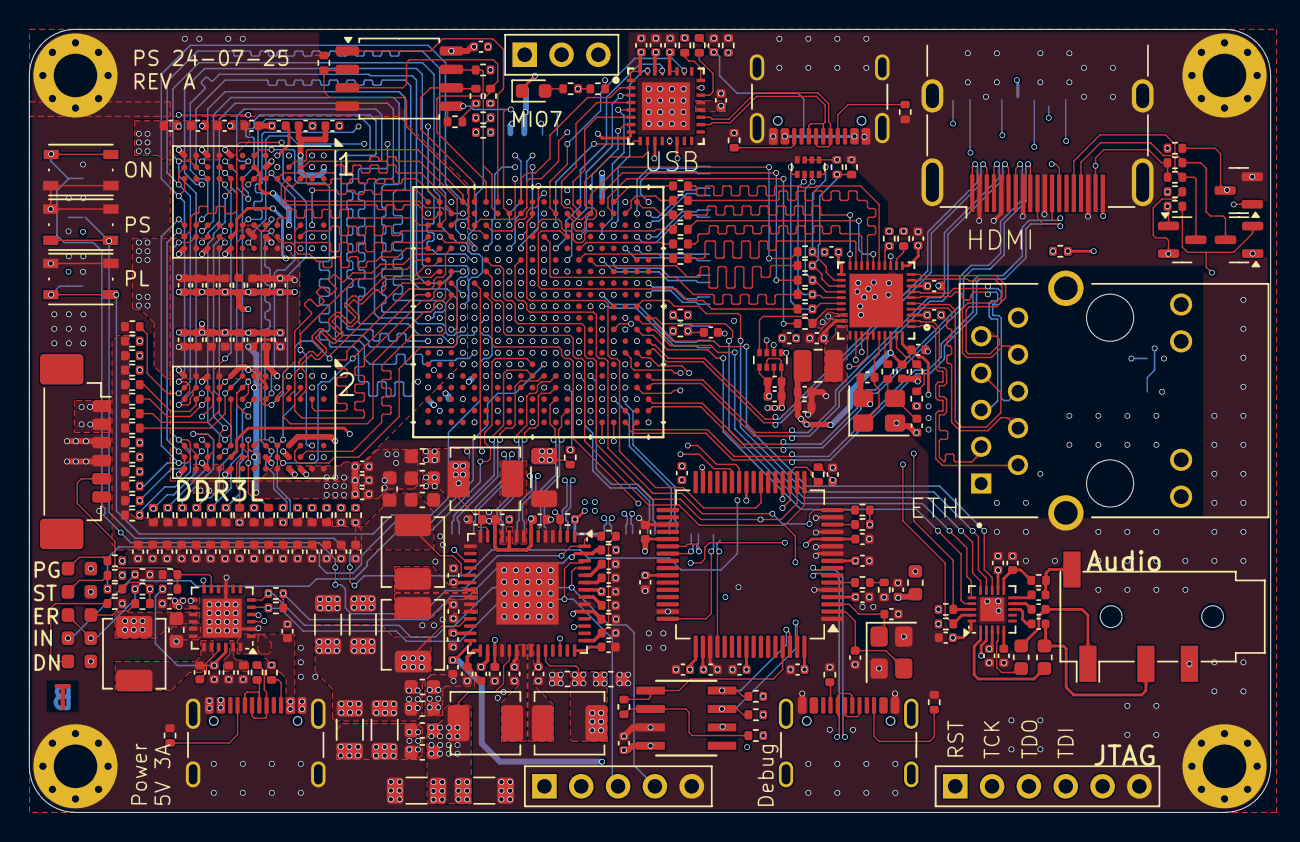
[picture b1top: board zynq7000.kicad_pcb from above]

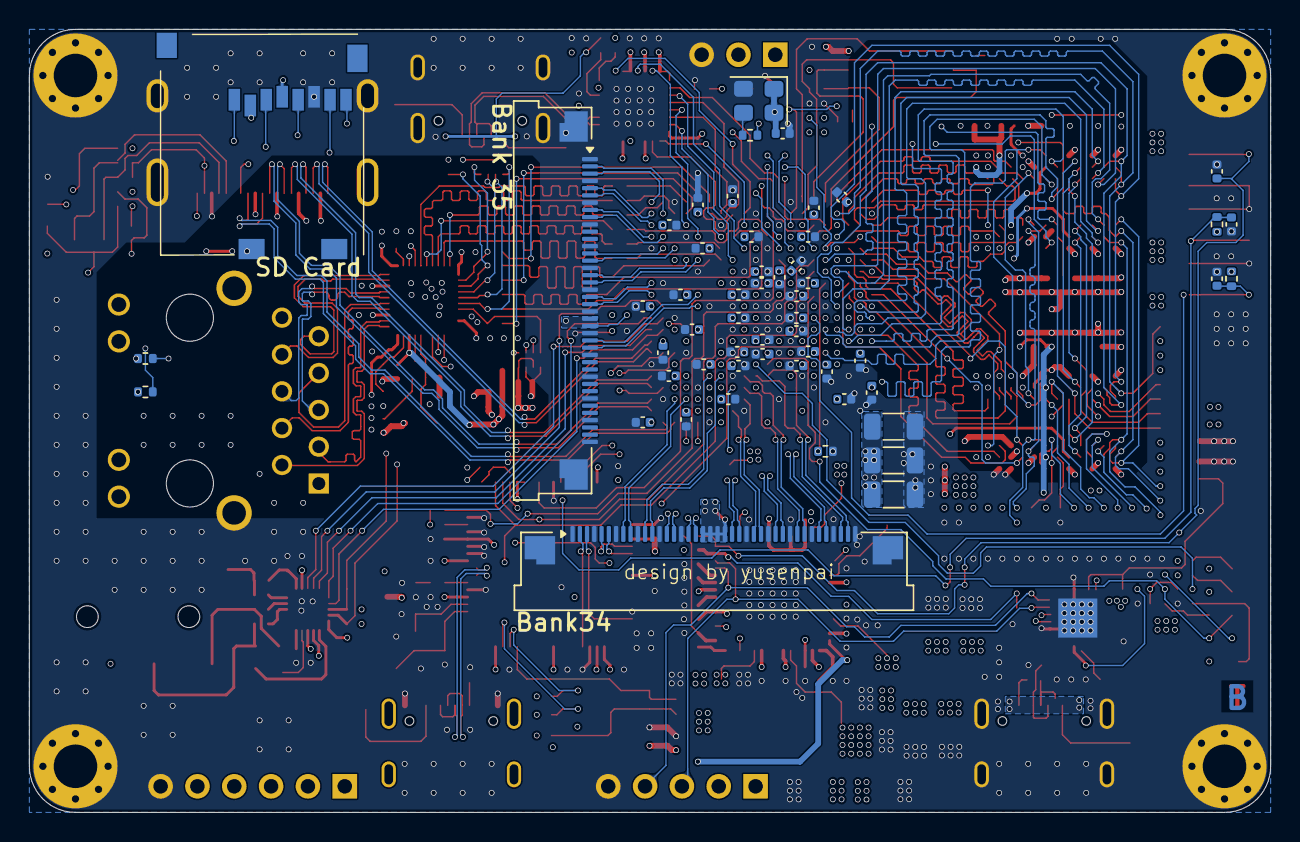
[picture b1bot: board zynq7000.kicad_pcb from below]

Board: 6 copper layers, 85.6 x 54.0 mm, 336 parts (54 on the bottom side), 280 nets.

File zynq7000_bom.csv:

"Reference"	"Value"	"Footprint"	"Qty"	"DNP"
"C1,C2,C3,C4,C5,C6,C7,C8,C10,C11,C12,C13,C14,C15,C16,C17,C18,C19,C20,C21,C22,C23,C24,C25,C26,C81,C94,C95,C96,C99,C100,C103,C106,C109,C112,C115,C119,C120,C121,C122,C124,C126,C127,C128,C129,C133,C134,C135,C136,C143,C172"	"470n"	"Capacitor_SMD:C_0402_1005Metric"	"51"	""
"C27,C28,C47"	"10n"	"Capacitor_SMD:C_0402_1005Metric"	"3"	""
"C29,C30,C87,C89,C144,C145,C149"	"10u"	"Capacitor_SMD:C_0402_1005Metric"	"7"	""
"C31,C32,C59,C60,C61,C62,C63,C64,C65,C88,C90,C91,C93,C98,C102,C105,C108,C111,C114,C117,C118,C125,C131,C132,C157,C168"	"4u7"	"Capacitor_SMD:C_0402_1005Metric"	"26"	""
"C33,C34,C35,C36,C37,C38,C39,C40,C41,C42,C43,C44,C45,C46,C48,C49,C50,C51,C54,C58,C72,C75,C80,C139,C140,C141,C142,C146,C147,C148,C150,C153,C154,C155,C156,C158,C159,C160,C161,C162,C163,C164,C165,C166,C167,C169"	"100n"	"Capacitor_SMD:C_0402_1005Metric"	"46"	""
"C52,C53,C55,C76,C79,C82,C84,C85,C152,C175,L1,L2,L3,L4,L5,L6"	"1u"	"Capacitor_SMD:C_0402_1005Metric,Inductor_SMD:L_Chilisin_BMRA00040420"	"16"	""
"C56,C57,C66,C67,C68,C69,C70,C71,C73,C74,C77,C78"	"22u"	"Capacitor_SMD:C_0603_1608Metric"	"12"	""
"C83"	"220n"	"Capacitor_SMD:C_0402_1005Metric"	"1"	""
"C86"	"47n"	"Capacitor_SMD:C_0402_1005Metric"	"1"	""
"C92,C97,C107,C110,C113"	"100u"	"Capacitor_SMD:C_1206_3216Metric"	"5"	""
"C101,C104,C116,C123,C130"	"47u"	"Capacitor_SMD:C_1206_3216Metric"	"5"	""
"C137,C138,C170,C171"	"10p"	"Capacitor_SMD:C_0402_1005Metric"	"4"	""
"C151,C174,L7"	"2u2"	"Capacitor_SMD:C_0402_1005Metric,Inductor_SMD:L_1008_2520Metric"	"3"	""
"D1,D4"	"RED"	"LED_SMD:LED_0603_1608Metric"	"2"	""
"D2"	"GREEN"	"LED_SMD:LED_0603_1608Metric"	"1"	""
"D3"	"BLUE"	"LED_SMD:LED_0603_1608Metric"	"1"	""
"D5"	"STAT"	"LED_SMD:LED_0603_1608Metric"	"1"	""
"D6"	"PG"	"LED_SMD:LED_0603_1608Metric"	"1"	""
"FB1"	"600R"	"Inductor_SMD:L_0603_1608Metric"	"1"	""
"IC1"	"MMPF0100NPAEP"	"Package_DFN_QFN:QFN-56-1EP_8x8mm_P0.5mm_EP4.3x4.3mm"	"1"	""
"J1,J2"	"FPC 40 pins P0.5mm"	"Connector_FFC-FPC:Amphenol_F32Q-1A7x1-11040_1x40-1MP_P0.5mm_Horizontal"	"2"	""
"J3,J5,J13"	"Header 2.54mm"	"Connector_PinHeader_2.54mm:PinHeader_1x03_P2.54mm_Vertical,Connector_PinHeader_2.54mm:PinHeader_1x05_P2.54mm_Vertical,Connector_PinHeader_2.54mm:PinHeader_1x06_P2.54mm_Vertical"	"3"	""
"J4"	"AudioJack4"	"Connector_Audio:Jack_3.5mm_PJ320D_Horizontal"	"1"	""
"J6,J9,J11"	"USB_C_Receptacle_USB2.0_16P"	"Connector_USB:USB_C_Receptacle_GCT_USB4105-xx-A_16P_TopMnt_Horizontal"	"3"	""
"J7"	"MX_1.25mm"	"Connector_Molex:Molex_PicoBlade_53398-0671_1x06-1MP_P1.25mm_Vertical"	"1"	""
"J8"	"HR911130A"	"Custom:HANRUN_HR911130A"	"1"	""
"J10"	"Micro_SD_Card_Det1"	"Custom:5008730806"	"1"	""
"J12"	"HDMI_A_1.4"	"Connector_Video:HDMI_A_Molex_208658-1001_Horizontal"	"1"	""
"Q1,Q2,Q3"	"2N7002"	"Package_TO_SOT_SMD:SOT-23"	"3"	""
"R1,R39,R41,R52,R68,R76,R77,R79,R81,R82,R91"	"1k"	"Resistor_SMD:R_0402_1005Metric"	"11"	""
"R2,R5,R19"	"120R"	"Resistor_SMD:R_0402_1005Metric"	"3"	""
"R3,R4"	"240R"	"Resistor_SMD:R_0402_1005Metric"	"2"	""
"R6,R7,R8,R35,R38,R40,R43,R50,R51,R54,R55,R56,R57,R75,R96,R97,R98,R99,R100"	"4k7"	"Resistor_SMD:R_0402_1005Metric"	"19"	""
"R9,R10,R11,R12,R13,R14,R15,R16,R17,R18,R20,R21,R22,R23,R24,R25,R26,R27,R28,R29,R30,R31,R32,R33"	"60R4"	"Resistor_SMD:R_0402_1005Metric"	"24"	""
"R34,R36,R37,R86,R90,R92,R93,R94"	"10k"	"Resistor_SMD:R_0402_1005Metric"	"8"	""
"R42"	"330R"	"Resistor_SMD:R_0402_1005Metric"	"1"	""
"R44,R45,R46,R47,R48,R49,R69,R70,R71,R72,R73,R74,R80,R108"	"22R"	"Resistor_SMD:R_0402_1005Metric"	"14"	""
"R53,R64,R65"	"2k2"	"Resistor_SMD:R_0402_1005Metric"	"3"	""
"R58"	"100k"	"Resistor_SMD:R_0402_1005Metric"	"1"	""
"R59"	"DNP"	"Resistor_SMD:R_0402_1005Metric"	"1"	""
"R60"	"DNP"	"Resistor_SMD:R_0402_1005Metric"	"1"	"DNP"
"R61,R62,R66,R83,R84,R87,R88"	"5k1"	"Resistor_SMD:R_0402_1005Metric"	"7"	""
"R63"	"0R"	"Resistor_SMD:R_0402_1005Metric"	"1"	"DNP"
"R67"	"30k"	"Resistor_SMD:R_0402_1005Metric"	"1"	""
"R78"	"2k49"	"Resistor_SMD:R_0402_1005Metric"	"1"	""
"R85"	"6k8"	"Resistor_SMD:R_0402_1005Metric"	"1"	""
"R89,R95"	"2k"	"Resistor_SMD:R_0402_1005Metric"	"2"	""
"R101,R102,R103,R104,R105,R106,R107"	"20k"	"Resistor_SMD:R_0402_1005Metric"	"7"	""
"R109"	"1k2"	"Resistor_SMD:R_0402_1005Metric"	"1"	""
"RN1,RN2"	"3k"	"Resistor_SMD:R_Array_Concave_4x0402"	"2"	""
"SW1,SW2,SW3"	"SW_Push"	"Button_Switch_SMD:SW_Push_1P1T_NO_Vertical_Wuerth_434133025816"	"3"	""
"U1"	"XC7Z010-1CLG400C"	"Custom:CLG400_XIL-L"	"1"	""
"U2,U3"	"H5TC2G83EFR-xxA"	"Package_BGA:FBGA-78_7.5x11mm_Layout2x3x13_P0.8mm"	"2"	""
"U4"	"SGTL5000XNLA3"	"Package_DFN_QFN:QFN-20-1EP_3x3mm_P0.4mm_EP1.65x1.65mm"	"1"	""
"U5"	"BQ25601"	"Package_DFN_QFN:Texas_RTW_WQFN-24-1EP_4x4mm_P0.5mm_EP2.7x2.7mm_ThermalVias"	"1"	""
"U6"	"RTL8211F-CG"	"Custom:RTL8211F-CG_RTK"	"1"	""
"U7"	"USB3320C-EZK-TR"	"Custom:QFN32_5X5MC_MCH"	"1"	""
"U8"	"W25Q128JVS"	"Package_SO:SOIC-8_5.3x5.3mm_P1.27mm"	"1"	""
"U9"	"FT4232H"	"Package_QFP:LQFP-64_10x10mm_P0.5mm"	"1"	""
"U10"	"AT93C46-10SU-2.7-T"	"Custom:SOIC8_4P9X3P9MC_MCH"	"1"	""
"X1"	"ASE-40MHz"	"Oscillator:Oscillator_SMD_Abracon_ASE-4Pin_3.2x2.5mm"	"1"	""
"Y1"	"25MHz"	"Crystal:Crystal_SMD_3225-4Pin_3.2x2.5mm"	"1"	""
"Y2"	"12MHz"	"Crystal:Crystal_SMD_3225-4Pin_3.2x2.5mm"	"1"	""

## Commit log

2025-07-26 add readme
2025-07-26 add demo
2025-07-27 add overview
